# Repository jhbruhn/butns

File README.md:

# Overview

small grid 64 clone heavily based on previous work by [hugelton/btns](https://github.com/hugelton/Btns).

Uses a Rasperry Pi Pico Microcontroller, NeoPixel RGB LEDs (SK6812), cheap buttons and a 3d-printed case and button-overlay.
Includes hardware and firmware support for an optional tilt-sensor.

# Building

It is highly recommended to order the PCB assembled from JLCPCB. That assembly will include everything other than the parts in the BOM.

## BOM

| Part                            | Quantity | Source                                                                                                                                                                                                                                                                                                                        | Required                      | 
|---------------------------------|----------|-------------------------------------------------------------------------------------------------------------------------------------------------------------------------------------------------------------------------------------------------------------------------------------------------------------------------------|-------------------------------|
| PCB with components             | 1        | JLCPCB, ordered with Gerber and Assembly files from latest release. Gerber: `butns-JLCPCB.zip`, BOM: `butns_bom_jlc.csv`, CPL: `butns_cpl_jlc.csv`.                                                                                                                                                                                                                                                            | yes                           | 
| Raspberry Pi Pico               | 1        | Original Raspberry Pi Pico, or [USB-C Variant](https://de.aliexpress.com/item/1005007393927221.html)                                                                                                                                                                                                                          | yes                           |   |
| M2.5x6 Button Head Screws       | 5        | [M2.5x6](https://www.aliexpress.com/item/32810852732.html)                                                                                                                                                                                                                                                                    | yes                           | 
| Case                        | 1        | 3d-printed (FDM). `case.stl` contains the top and bottom half. In the image, it is printed in black PLA, 0.2mm layerheight.                                                                                                                                                                                                   | yes                           | 
| Button Matrix                     | 1        | 3d-printed (FDM). Print `buttons.stl` with white PLA and 0.12mm layerheight and no infill, 2 wall lines, concentric top infill. These should guide the LEDs light well. Optional: Add `buttons-black-blockers.stl` while importing as a multi-material print and print those in black to block light from neighboring buttons | yes (black blockers optional) | 
| Button TPU Case Inlay         | 1        | 3d-printed (FDM). Print with TPU, perhaps in black. Will help against rattling of the buttons in the case.                                                                                                                                                                                                                    | no                            | 
| SMD 2.54" Pin Header 1x8 Type A | 1        | [1x8 Type A](https://www.aliexpress.com/item/1005005203849802.html)                                                                                                                                                                                                                                                           | no, for tilt                  | 
| MPU6050 module                  | 1        | [MPU6050 Module](https://www.aliexpress.com/item/1005006396343851.html)                                                                                                                                                                                                                                                       | no, for tilt                  | 

## Assembly

Flash microcontroller with `firmware.uf2`. Solder MCU and Pin-Header to PCB. Screw everything into the case. Done!

Hint: The cases Top half has one specific orientation where it fits nicely: The top-screw-posts of the top-half with the larger cutoaways go to the side opposite of the USB Connector.

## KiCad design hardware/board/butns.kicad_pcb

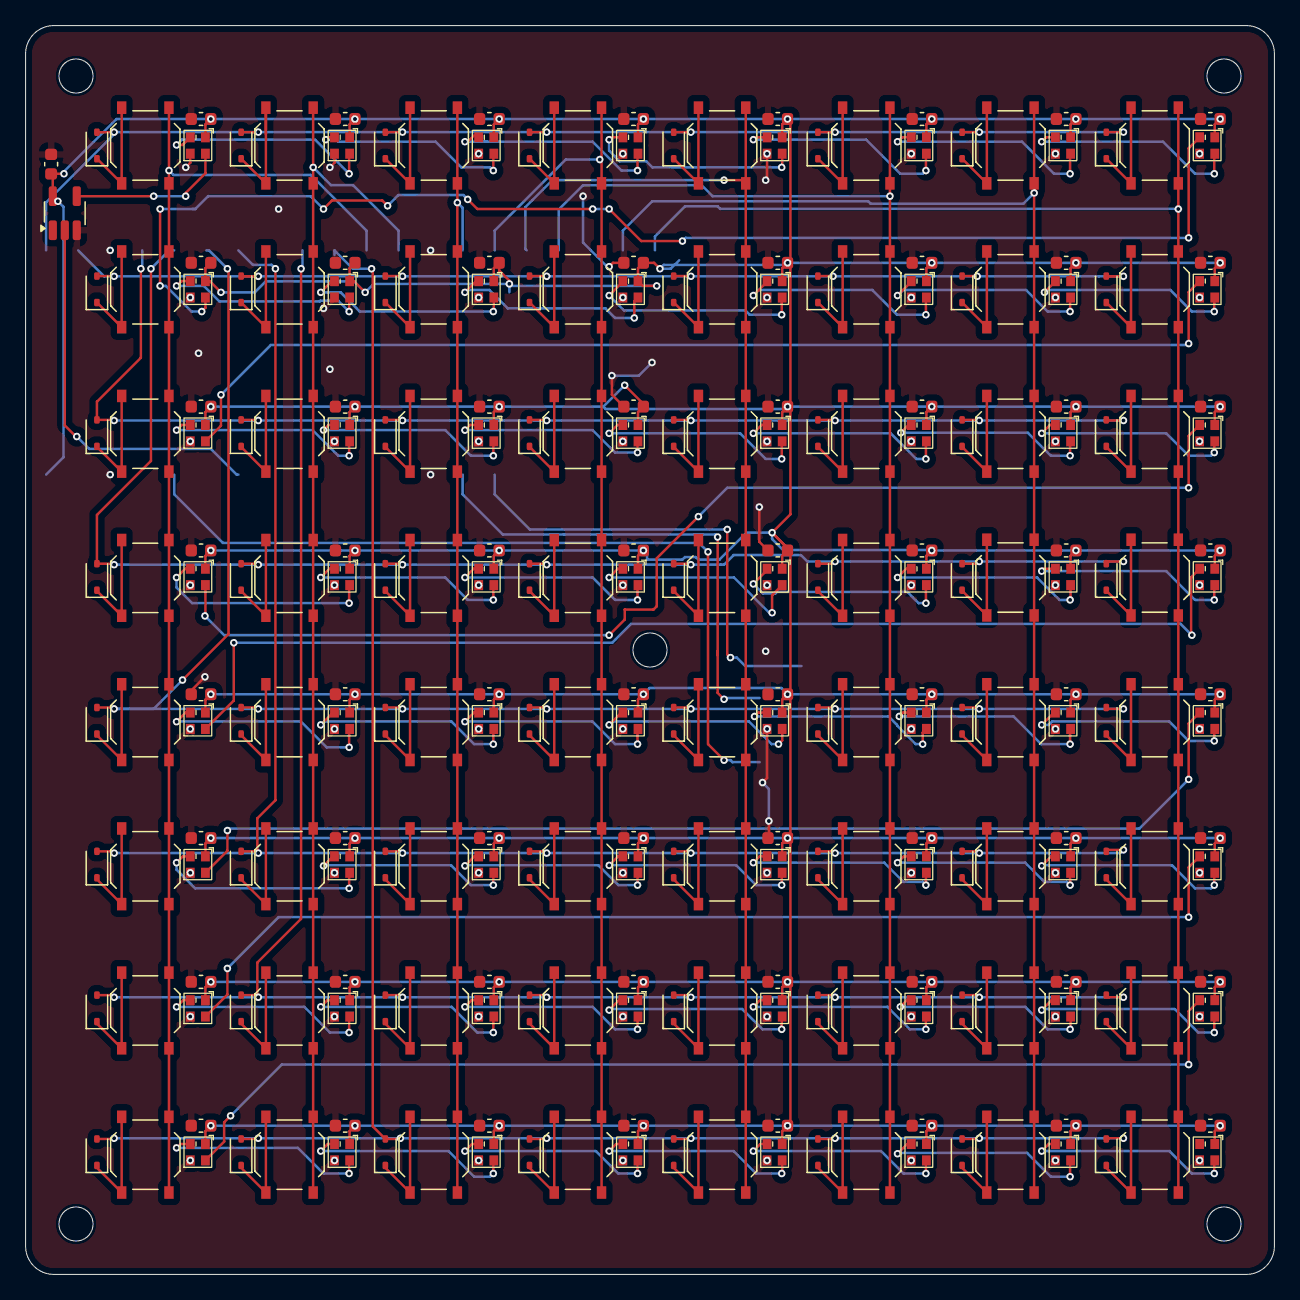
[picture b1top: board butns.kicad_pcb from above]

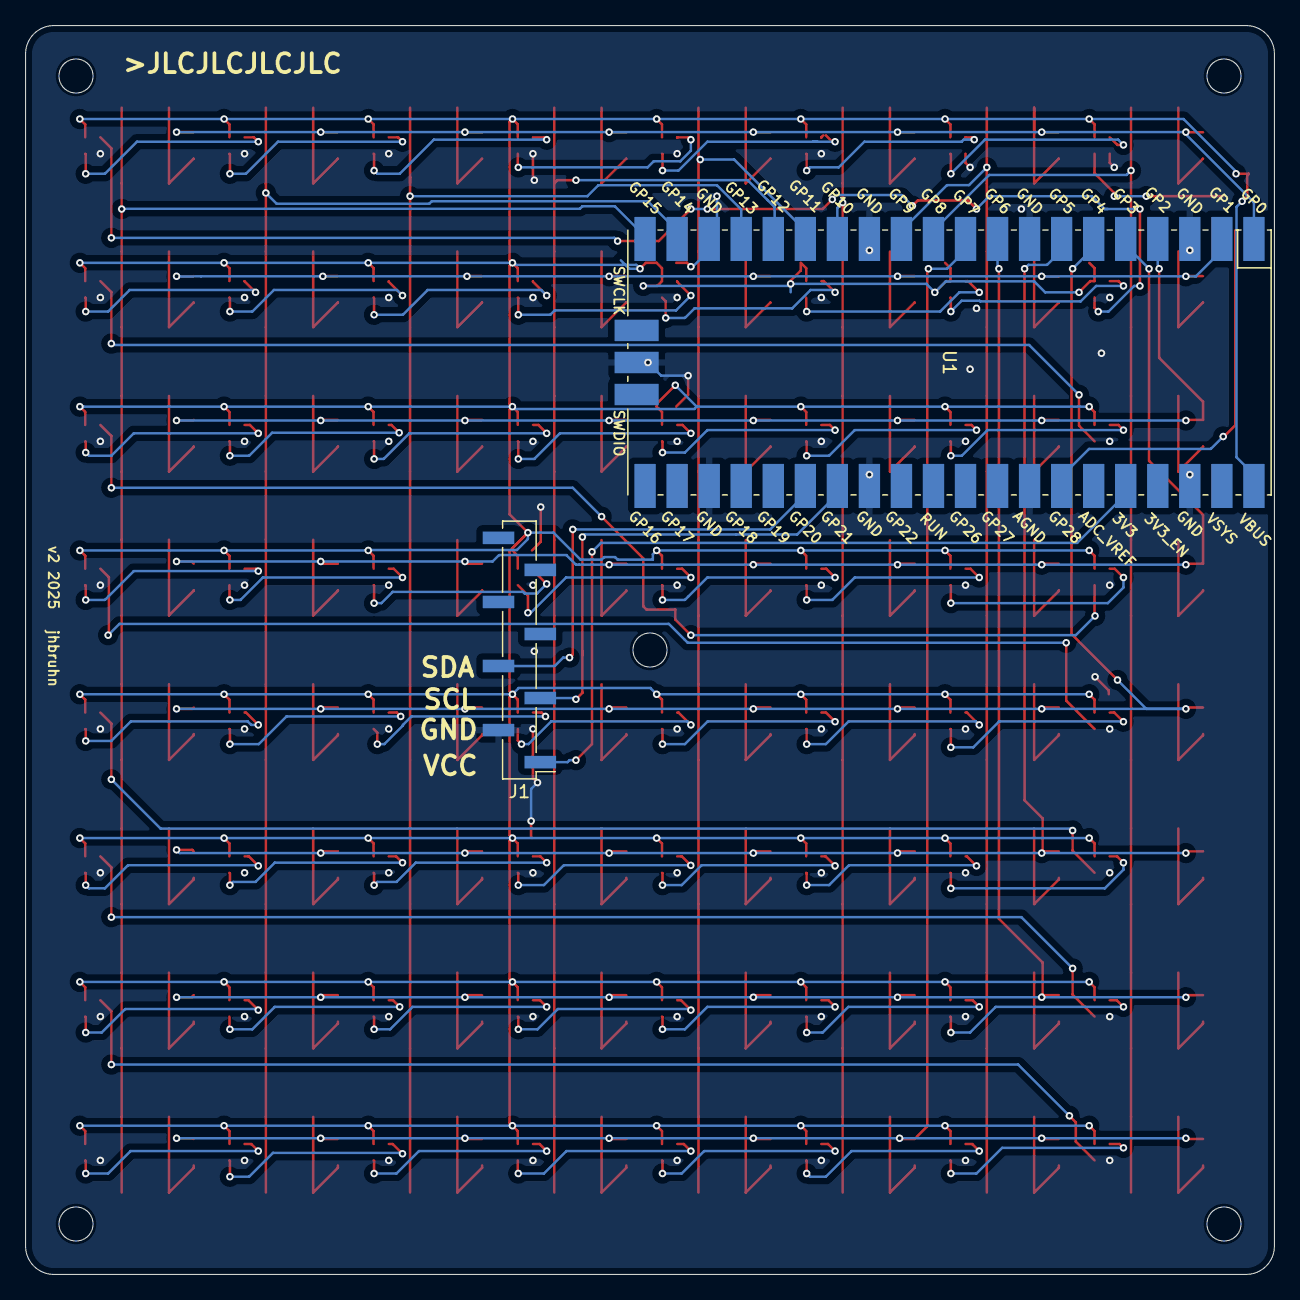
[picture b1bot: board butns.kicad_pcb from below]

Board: 2 copper layers, 99.0 x 99.0 mm, 265 parts (2 on the bottom side), 150 nets.

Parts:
C1, C2, C3, C4, C5, C6, C7, C8, C9, C10, C11, C12, C13, C14, C15, C16, C17, C18, C19, C20, C21, C22, C23, C24, C25, C26, C27, C28, C29, C30, C31, C32, C33, C34, C35, C36, C37, C38, C39, C40, C41, C42, C43, C44, C45, C46, C47, C48, C49, C50, C51, C52, C53, C54, C55, C56, C57, C58, C59, C60, C61, C62, C63, C64, C65: 100nF; C_0603_1608Metric
D1, D66, D67, D68, D69, D70, D71, D72, D73, D74, D75, D76, D77, D78, D79, D80, D81, D82, D83, D84, D85, D86, D87, D88, D89, D90, D91, D92, D93, D94, D95, D96, D97, D98, D99, D100, D101, D102, D103, D104, D105, D106, D107, D108, D109, D110, D111, D112, D113, D114, D115, D116, D117, D118, D119, D120, D121, D122, D123, D124, D125, D126, D127, D128: SK6812-EC20
D2, D3, D4, D5, D6, D7, D8, D9, D10, D11, D12, D13, D14, D15, D16, D17, D18, D19, D20, D21, D22, D23, D24, D25, D26, D27, D28, D29, D30, D31, D32, D33, D34, D35, D36, D37, D38, D39, D40, D41, D42, D43, D44, D45, D46, D47, D48, D49, D50, D51, D52, D53, D54, D55, D56, D57, D58, D59, D60, D61, D62, D63, D64, D65: 1N4148WS; D_SOD-323
H1, H2, H3, H4, H5: MountingHole; MountingHole_2.7mm_M2.5
J1: Conn_01x08; PinHeader_1x08_P2.54mm_Vertical_SMD_Pin1Left
SW1, SW2, SW3, SW4, SW5, SW6, SW7, SW8, SW9, SW10, SW11, SW12, SW13, SW14, SW15, SW16, SW17, SW18, SW19, SW20, SW21, SW22, SW23, SW24, SW25, SW26, SW27, SW28, SW29, SW30, SW31, SW32, SW33, SW34, SW35, SW36, SW37, SW38, SW39, SW40, SW41, SW42, SW43, SW44, SW45, SW46, SW47, SW48, SW49, SW50, SW51, SW52, SW53, SW54, SW55, SW56, SW57, SW58, SW59, SW60, SW61, SW62, SW63, SW64: SW_Push; SW_Push_1P1T_XKB_TS-1187A
U1: Pico; RPi_Pico_SMD_TH
U2: 74LVC1G17; SOT-23-5_HandSoldering

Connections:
+3.3V: J1.1, U1.36 (3V3)
+5V: C1.1, C2.1, C3.1, C4.1, C5.1, C6.1, C7.1, C8.1, C9.1, C10.1, C11.1, C12.1, C13.1, C14.1, C15.1, C16.1, C17.1, C18.1, C19.1, C20.1, C21.1, C22.1, C23.1, C24.1, C25.1, C26.1, C27.1, C28.1, C29.1, C30.1, C31.1, C32.1, C33.1, C34.1, C35.1, C36.1, C37.1, C38.1, C39.1, C40.1, C41.1, C42.1, C43.1, C44.1, C45.1, C46.1, C47.1, C48.1, C49.1, C50.1, C51.1, C52.1, C53.1, C54.1, C55.1, C56.1, C57.1, C58.1, C59.1, C60.1, C61.1, C62.1, C63.1, C64.1, C65.1, D1.1 (VDD), D66.1 (VDD), D67.1 (VDD), D68.1 (VDD), D69.1 (VDD), D70.1 (VDD), D71.1 (VDD), D72.1 (VDD), D73.1 (VDD), D74.1 (VDD), D75.1 (VDD), D76.1 (VDD), D77.1 (VDD), D78.1 (VDD), D79.1 (VDD), D80.1 (VDD), D81.1 (VDD), D82.1 (VDD), D83.1 (VDD), D84.1 (VDD), D85.1 (VDD), D86.1 (VDD), D87.1 (VDD), D88.1 (VDD), D89.1 (VDD), D90.1 (VDD), D91.1 (VDD), D92.1 (VDD), D93.1 (VDD), D94.1 (VDD), D95.1 (VDD), D96.1 (VDD), D97.1 (VDD), D98.1 (VDD), D99.1 (VDD), D100.1 (VDD), D101.1 (VDD), D102.1 (VDD), D103.1 (VDD), D104.1 (VDD), D105.1 (VDD), D106.1 (VDD), D107.1 (VDD), D108.1 (VDD), D109.1 (VDD), D110.1 (VDD), D111.1 (VDD), D112.1 (VDD), D113.1 (VDD), D114.1 (VDD), D115.1 (VDD), D116.1 (VDD), D117.1 (VDD), D118.1 (VDD), D119.1 (VDD), D120.1 (VDD), D121.1 (VDD), D122.1 (VDD), D123.1 (VDD), D124.1 (VDD), D125.1 (VDD), D126.1 (VDD), D127.1 (VDD), D128.1 (VDD), U1.40 (VBUS), U2.5 (VCC)
GND: C1.2, C2.2, C3.2, C4.2, C5.2, C6.2, C7.2, C8.2, C9.2, C10.2, C11.2, C12.2, C13.2, C14.2, C15.2, C16.2, C17.2, C18.2, C19.2, C20.2, C21.2, C22.2, C23.2, C24.2, C25.2, C26.2, C27.2, C28.2, C29.2, C30.2, C31.2, C32.2, C33.2, C34.2, C35.2, C36.2, C37.2, C38.2, C39.2, C40.2, C41.2, C42.2, C43.2, C44.2, C45.2, C46.2, C47.2, C48.2, C49.2, C50.2, C51.2, C52.2, C53.2, C54.2, C55.2, C56.2, C57.2, C58.2, C59.2, C60.2, C61.2, C62.2, C63.2, C64.2, C65.2, D1.3 (VSS), D66.3 (VSS), D67.3 (VSS), D68.3 (VSS), D69.3 (VSS), D70.3 (VSS), D71.3 (VSS), D72.3 (VSS), D73.3 (VSS), D74.3 (VSS), D75.3 (VSS), D76.3 (VSS), D77.3 (VSS), D78.3 (VSS), D79.3 (VSS), D80.3 (VSS), D81.3 (VSS), D82.3 (VSS), D83.3 (VSS), D84.3 (VSS), D85.3 (VSS), D86.3 (VSS), D87.3 (VSS), D88.3 (VSS), D89.3 (VSS), D90.3 (VSS), D91.3 (VSS), D92.3 (VSS), D93.3 (VSS), D94.3 (VSS), D95.3 (VSS), D96.3 (VSS), D97.3 (VSS), D98.3 (VSS), D99.3 (VSS), D100.3 (VSS), D101.3 (VSS), D102.3 (VSS), D103.3 (VSS), D104.3 (VSS), D105.3 (VSS), D106.3 (VSS), D107.3 (VSS), D108.3 (VSS), D109.3 (VSS), D110.3 (VSS), D111.3 (VSS), D112.3 (VSS), D113.3 (VSS), D114.3 (VSS), D115.3 (VSS), D116.3 (VSS), D117.3 (VSS), D118.3 (VSS), D119.3 (VSS), D120.3 (VSS), D121.3 (VSS), D122.3 (VSS), D123.3 (VSS), D124.3 (VSS), D125.3 (VSS), D126.3 (VSS), D127.3 (VSS), D128.3 (VSS), J1.2, U1.3 (GND), U1.8 (GND), U1.13 (GND), U1.18 (GND), U1.23 (GND), U1.28 (GND), U1.33 (AGND), U1.38 (GND), U1.42 (GND), U2.3 (GND)
I2C0_SCL: J1.3, U1.27 (GPIO21)
I2C0_SDA: J1.4, U1.26 (GPIO20)
LED_DATA: U1.34 (GPIO28_ADC2), U2.2
LED_DIN: D1.4 (DIN), U2.4
unnamed: D1.2 (DOUT), D66.4 (DIN)
unnamed: D2.1 (K), SW1.1
unnamed: D3.1 (K), SW2.1
unnamed: D4.1 (K), SW3.1
unnamed: D5.1 (K), SW4.1
unnamed: D6.1 (K), SW5.1
unnamed: D7.1 (K), SW6.1
unnamed: D8.1 (K), SW7.1
unnamed: D9.1 (K), SW8.1
unnamed: D10.1 (K), SW9.1
unnamed: D11.1 (K), SW10.1
unnamed: D12.1 (K), SW11.1
unnamed: D13.1 (K), SW12.1
unnamed: D14.1 (K), SW13.1
unnamed: D15.1 (K), SW14.1
unnamed: D16.1 (K), SW15.1
unnamed: D17.1 (K), SW16.1
unnamed: D18.1 (K), SW17.1
unnamed: D19.1 (K), SW18.1
unnamed: D20.1 (K), SW19.1
unnamed: D21.1 (K), SW20.1
unnamed: D22.1 (K), SW21.1
unnamed: D23.1 (K), SW22.1
unnamed: D24.1 (K), SW23.1
unnamed: D25.1 (K), SW24.1
unnamed: D26.1 (K), SW25.1
unnamed: D27.1 (K), SW26.1
unnamed: D28.1 (K), SW27.1
unnamed: D29.1 (K), SW28.1
unnamed: D30.1 (K), SW29.1
unnamed: D31.1 (K), SW30.1
unnamed: D32.1 (K), SW31.1
unnamed: D33.1 (K), SW32.1
unnamed: D34.1 (K), SW33.1
unnamed: D35.1 (K), SW34.1
unnamed: D36.1 (K), SW35.1
unnamed: D37.1 (K), SW36.1
unnamed: D38.1 (K), SW37.1
unnamed: D39.1 (K), SW38.1
unnamed: D40.1 (K), SW39.1
unnamed: D41.1 (K), SW40.1
unnamed: D42.1 (K), SW41.1
unnamed: D43.1 (K), SW42.1
unnamed: D44.1 (K), SW43.1
unnamed: D45.1 (K), SW44.1
unnamed: D46.1 (K), SW45.1
unnamed: D47.1 (K), SW46.1
unnamed: D48.1 (K), SW47.1
unnamed: D49.1 (K), SW48.1
unnamed: D50.1 (K), SW49.1
unnamed: D51.1 (K), SW50.1
unnamed: D52.1 (K), SW51.1
unnamed: D53.1 (K), SW52.1
unnamed: D54.1 (K), SW53.1
unnamed: D55.1 (K), SW54.1
unnamed: D56.1 (K), SW55.1
unnamed: D57.1 (K), SW56.1
unnamed: D58.1 (K), SW57.1
unnamed: D59.1 (K), SW58.1
unnamed: D60.1 (K), SW59.1
unnamed: D61.1 (K), SW60.1
unnamed: D62.1 (K), SW61.1
unnamed: D63.1 (K), SW62.1
unnamed: D64.1 (K), SW63.1
unnamed: D65.1 (K), SW64.1
unnamed: D66.2 (DOUT), D67.4 (DIN)
unnamed: D67.2 (DOUT), D68.4 (DIN)
unnamed: D68.2 (DOUT), D69.4 (DIN)
unnamed: D69.2 (DOUT), D70.4 (DIN)
unnamed: D70.2 (DOUT), D71.4 (DIN)
unnamed: D71.2 (DOUT), D72.4 (DIN)
unnamed: D72.2 (DOUT), D73.4 (DIN)
unnamed: D73.2 (DOUT), D74.4 (DIN)
unnamed: D74.2 (DOUT), D75.4 (DIN)
unnamed: D75.2 (DOUT), D76.4 (DIN)
unnamed: D76.2 (DOUT), D77.4 (DIN)
unnamed: D77.2 (DOUT), D78.4 (DIN)
unnamed: D78.2 (DOUT), D79.4 (DIN)
unnamed: D79.2 (DOUT), D80.4 (DIN)
unnamed: D80.2 (DOUT), D81.4 (DIN)
unnamed: D81.2 (DOUT), D82.4 (DIN)
unnamed: D82.2 (DOUT), D83.4 (DIN)
unnamed: D83.2 (DOUT), D84.4 (DIN)
unnamed: D84.2 (DOUT), D85.4 (DIN)
unnamed: D85.2 (DOUT), D86.4 (DIN)
unnamed: D86.2 (DOUT), D87.4 (DIN)
unnamed: D87.2 (DOUT), D88.4 (DIN)
unnamed: D88.2 (DOUT), D89.4 (DIN)
unnamed: D89.2 (DOUT), D90.4 (DIN)
unnamed: D90.2 (DOUT), D91.4 (DIN)
unnamed: D91.2 (DOUT), D92.4 (DIN)
unnamed: D92.2 (DOUT), D93.4 (DIN)
unnamed: D93.2 (DOUT), D94.4 (DIN)
unnamed: D94.2 (DOUT), D95.4 (DIN)
unnamed: D95.2 (DOUT), D96.4 (DIN)
unnamed: D96.2 (DOUT), D97.4 (DIN)
unnamed: D97.2 (DOUT), D98.4 (DIN)
unnamed: D98.2 (DOUT), D99.4 (DIN)
unnamed: D99.2 (DOUT), D100.4 (DIN)
unnamed: D100.2 (DOUT), D101.4 (DIN)
unnamed: D101.2 (DOUT), D102.4 (DIN)
unnamed: D102.2 (DOUT), D103.4 (DIN)
unnamed: D103.2 (DOUT), D104.4 (DIN)
unnamed: D104.2 (DOUT), D105.4 (DIN)
unnamed: D105.2 (DOUT), D106.4 (DIN)
unnamed: D106.2 (DOUT), D107.4 (DIN)
unnamed: D107.2 (DOUT), D108.4 (DIN)
unnamed: D108.2 (DOUT), D109.4 (DIN)
unnamed: D109.2 (DOUT), D110.4 (DIN)
unnamed: D110.2 (DOUT), D111.4 (DIN)
unnamed: D111.2 (DOUT), D112.4 (DIN)
unnamed: D112.2 (DOUT), D113.4 (DIN)
unnamed: D113.2 (DOUT), D114.4 (DIN)
unnamed: D114.2 (DOUT), D115.4 (DIN)
unnamed: D115.2 (DOUT), D116.4 (DIN)
unnamed: D116.2 (DOUT), D117.4 (DIN)
unnamed: D117.2 (DOUT), D118.4 (DIN)
unnamed: D118.2 (DOUT), D119.4 (DIN)
unnamed: D119.2 (DOUT), D120.4 (DIN)
unnamed: D120.2 (DOUT), D121.4 (DIN)
unnamed: D121.2 (DOUT), D122.4 (DIN)
unnamed: D122.2 (DOUT), D123.4 (DIN)
unnamed: D123.2 (DOUT), D124.4 (DIN)
unnamed: D124.2 (DOUT), D125.4 (DIN)
unnamed: D125.2 (DOUT), D126.4 (DIN)
unnamed: D126.2 (DOUT), D127.4 (DIN)
unnamed: D127.2 (DOUT), D128.4 (DIN)
SW_COL_1: SW1.2, SW9.2, SW17.2, SW25.2, SW33.2, SW41.2, SW49.2, SW57.2, U1.11 (GPIO8)
SW_COL_2: SW2.2, SW10.2, SW18.2, SW26.2, SW34.2, SW42.2, SW50.2, SW58.2, U1.12 (GPIO9)
SW_COL_3: SW3.2, SW11.2, SW19.2, SW27.2, SW35.2, SW43.2, SW51.2, SW59.2, U1.14 (GPIO10)
SW_COL_4: SW4.2, SW12.2, SW20.2, SW28.2, SW36.2, SW44.2, SW52.2, SW60.2, U1.15 (GPIO11)
SW_COL_5: SW5.2, SW13.2, SW21.2, SW29.2, SW37.2, SW45.2, SW53.2, SW61.2, U1.16 (GPIO12)
SW_COL_6: SW6.2, SW14.2, SW22.2, SW30.2, SW38.2, SW46.2, SW54.2, SW62.2, U1.17 (GPIO13)
SW_COL_7: SW7.2, SW15.2, SW23.2, SW31.2, SW39.2, SW47.2, SW55.2, SW63.2, U1.19 (GPIO14)
SW_COL_8: SW8.2, SW16.2, SW24.2, SW32.2, SW40.2, SW48.2, SW56.2, SW64.2, U1.20 (GPIO15)
SW_ROW_1: D2.2 (A), D3.2 (A), D4.2 (A), D5.2 (A), D6.2 (A), D7.2 (A), D8.2 (A), D9.2 (A), U1.1 (GPIO0)
SW_ROW_2: D10.2 (A), D11.2 (A), D12.2 (A), D13.2 (A), D14.2 (A), D15.2 (A), D16.2 (A), D17.2 (A), U1.2 (GPIO1)
SW_ROW_3: D18.2 (A), D19.2 (A), D20.2 (A), D21.2 (A), D22.2 (A), D23.2 (A), D24.2 (A), D25.2 (A), U1.4 (GPIO2)
SW_ROW_4: D26.2 (A), D27.2 (A), D28.2 (A), D29.2 (A), D30.2 (A), D31.2 (A), D32.2 (A), D33.2 (A), U1.5 (GPIO3)
SW_ROW_5: D34.2 (A), D35.2 (A), D36.2 (A), D37.2 (A), D38.2 (A), D39.2 (A), D40.2 (A), D41.2 (A), U1.6 (GPIO4)
SW_ROW_6: D42.2 (A), D43.2 (A), D44.2 (A), D45.2 (A), D46.2 (A), D47.2 (A), D48.2 (A), D49.2 (A), U1.7 (GPIO5)
SW_ROW_7: D50.2 (A), D51.2 (A), D52.2 (A), D53.2 (A), D54.2 (A), D55.2 (A), D56.2 (A), D57.2 (A), U1.9 (GPIO6)
SW_ROW_8: D58.2 (A), D59.2 (A), D60.2 (A), D61.2 (A), D62.2 (A), D63.2 (A), D64.2 (A), D65.2 (A), U1.10 (GPIO7)

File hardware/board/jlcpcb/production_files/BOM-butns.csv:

Comment,Designator,Footprint,LCSC,Quantity
100nF,"C1,C10,C11,C12,C13,C14,C15,C16,C17,C18,C19,C2,C20,C21,C22,C23,C24,C25,C26,C27,C28,C29,C3,C30,C31,C32,C33,C34,C35,C36,C37,C38,C39,C4,C40,C41,C42,C43,C44,C45,C46,C47,C48,C49,C5,C50,C51,C52,C53,C54,C55,C56,C57,C58,C59,C6,C60,C61,C62,C63,C64,C65,C7,C8,C9",C_0603_1608Metric,C14663,65
1N4148WS,"D10,D11,D12,D13,D14,D15,D16,D17,D18,D19,D2,D20,D21,D22,D23,D24,D25,D26,D27,D28,D29,D3,D30,D31,D32,D33,D34,D35,D36,D37,D38,D39,D4,D40,D41,D42,D43,D44,D45,D46,D47,D48,D49,D5,D50,D51,D52,D53,D54,D55,D56,D57,D58,D59,D6,D60,D61,D62,D63,D64,D65,D7,D8,D9",D_SOD-323,C2128,64
SK6812-EC20,"D1,D100,D101,D102,D103,D104,D105,D106,D107,D108,D109,D110,D111,D112,D113,D114,D115,D116,D117,D118,D119,D120,D121,D122,D123,D124,D125,D126,D127,D128,D66,D67,D68,D69,D70,D71,D72,D73,D74,D75,D76,D77,D78,D79,D80,D81,D82,D83,D84,D85,D86,D87,D88,D89,D90,D91,D92,D93,D94,D95,D96,D97,D98,D99",SK6812-EC20,C2909058,64
SW_Push,"SW1,SW10,SW11,SW12,SW13,SW14,SW15,SW16,SW17,SW18,SW19,SW2,SW20,SW21,SW22,SW23,SW24,SW25,SW26,SW27,SW28,SW29,SW3,SW30,SW31,SW32,SW33,SW34,SW35,SW36,SW37,SW38,SW39,SW4,SW40,SW41,SW42,SW43,SW44,SW45,SW46,SW47,SW48,SW49,SW5,SW50,SW51,SW52,SW53,SW54,SW55,SW56,SW57,SW58,SW59,SW6,SW60,SW61,SW62,SW63,SW64,SW7,SW8,SW9",SW_Push_1P1T_XKB_TS-1187A,C318884,64
74LVC1G17,U2,SOT-23-5_HandSoldering,C7836,1
Conn_01x08,J1,PinHeader_1x08_P2.54mm_Vertical_SMD_Pin1Left,,1
Pico,U1,RPi_Pico_SMD_TH,,1

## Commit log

2025-02-08 Fix action syntax
2025-02-08 Fix name of platform
2025-02-08 Fix library names
2025-02-08 Fix FQBN
2025-02-08 Add board option
2025-02-08 Switch to pio
2025-02-08 Upload firmware after compiling
2025-02-08 Use newer artifact action
2025-02-08 Make firmware.cpp from firmware.ino
2025-02-08 License adjustment and python version
2025-02-08 Correctly move include files
2025-02-08 Move files around, add case build job test
2025-02-08 Rename case stls workflow
2025-02-08 Different action version
2025-02-08 Also checkout submodules
2025-02-08 Add parameter sets and jobs for buttons
2025-02-08 Use newer openscad version
2025-02-08 Actually use nightly version of openscad
2025-02-08 Add release workflow
2025-02-08 Fix syntax
2025-02-08 fix job order
2025-02-08 Restructure workflows
2025-02-08 Add explicit permission to gh release action
2025-02-08 Fix tag thingy
2025-02-08 remove remains
2025-02-08 Add CI for kicad
2025-02-08 Fix path for release job
2025-02-14 Implement Tilt Sensor support
2025-02-14 Add Readme
2025-02-14 Remove Buttons Silkscreen name, update version
2025-02-14 Add hint on top case orientation
2025-02-14 Remove last column from bom
